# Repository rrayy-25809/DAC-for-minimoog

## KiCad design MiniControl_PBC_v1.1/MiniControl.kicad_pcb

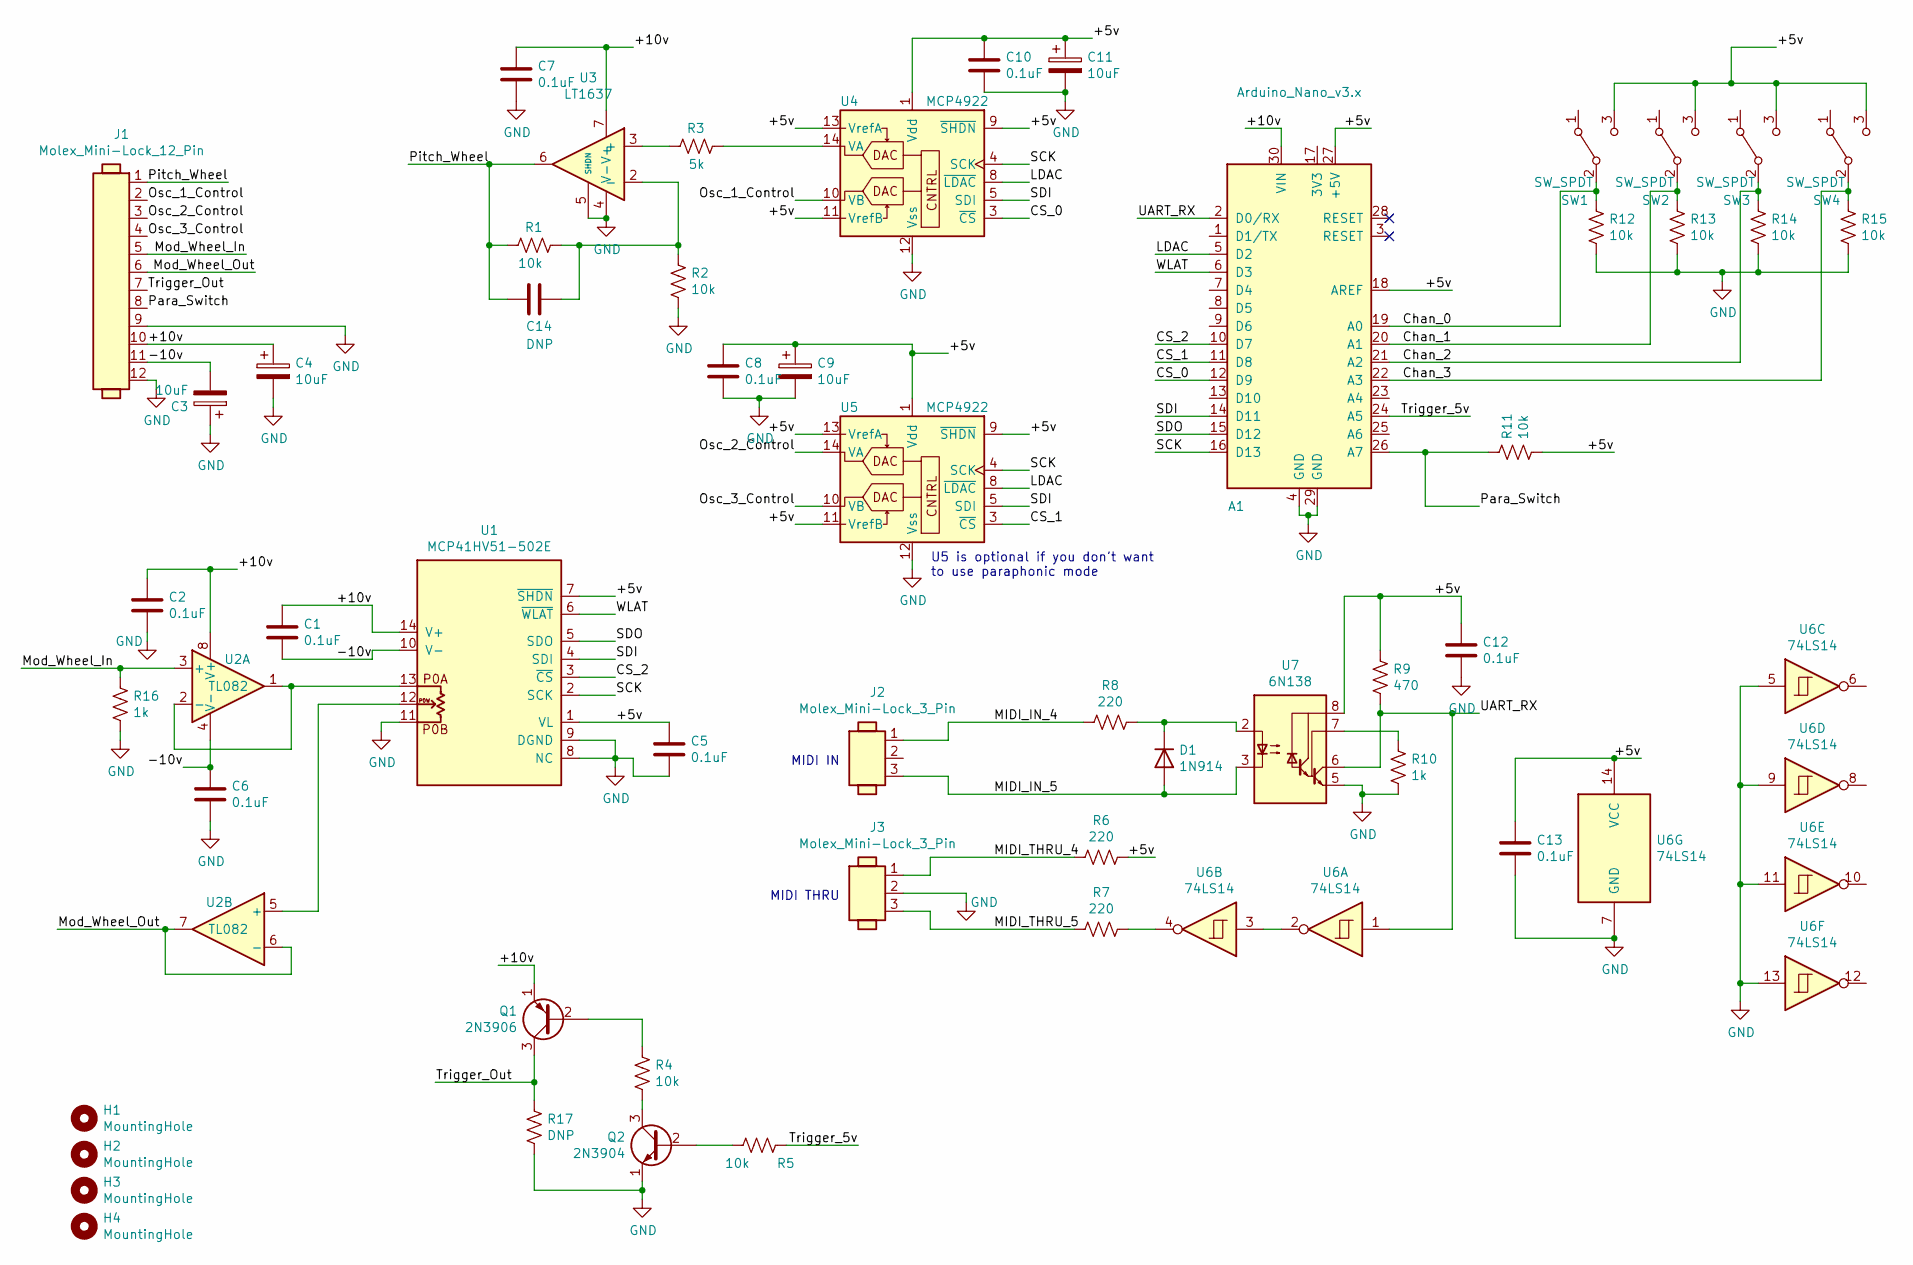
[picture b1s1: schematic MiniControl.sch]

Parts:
A1: Arduino_Nano_v3.x; Arduino_Nano
C1, C2, C5, C6, C7, C8, C10, C12, C13: 0.1uF; C_Disc_D5.1mm_W3.2mm_P5.00mm
C3, C4, C9, C11: 10uF; CP_Radial_Tantal_D6.0mm_P5.00mm
C14: DNP; C_Disc_D5.1mm_W3.2mm_P5.00mm
D1: 1N914; D_DO-35_SOD27_P7.62mm_Horizontal
H1, H2, H3, H4: MountingHole; MountingHole_3.2mm_M3
J1: Molex_Mini-Lock_12_Pin; Molex_Mini-Lock_0534261210_1x12_P2.50mm_Horizontal; Part # 0534261210
J2, J3: Molex_Mini-Lock_3_Pin; Molex_Mini-Lock_0534260310_1x03_P2.50mm_Horizontal; Part # 0534260310
Q1: 2N3906; TO-92_Inline
Q2: 2N3904; TO-92_Inline
R1, R2, R4, R5, R11, R12, R13, R14, R15: 10k; R_Axial_DIN0207_L6.3mm_D2.5mm_P10.16mm_Horizontal
R3: 5k; R_Axial_DIN0207_L6.3mm_D2.5mm_P10.16mm_Horizontal
R6, R7, R8: 220; R_Axial_DIN0207_L6.3mm_D2.5mm_P10.16mm_Horizontal
R9: 470; R_Axial_DIN0207_L6.3mm_D2.5mm_P10.16mm_Horizontal
R10, R16: 1k; R_Axial_DIN0207_L6.3mm_D2.5mm_P10.16mm_Horizontal
R17: DNP; R_Axial_DIN0207_L6.3mm_D2.5mm_P10.16mm_Horizontal
SW1, SW2, SW3, SW4: SW_SPDT; SW_Slide_SPDT_EG1218
U1: MCP41HV51-502E; TSSOP-14_4.4x5mm_P0.65mm
U2: TL082; DIP-8_W7.62mm_Socket
U3: LT1637; DIP-8_W7.62mm_Socket
U4, U5: MCP4922; DIP-14_W7.62mm_Socket
U6: 74LS14; DIP-14_W7.62mm_Socket
U7: 6N138; DIP-8_W7.62mm_Socket

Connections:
/+5v: A1.18 (AREF), A1.27 (+5V), C5.1, C8.1, C9.1, C10.1, C11.1, C12.1, C13.1, R6.2, R9.1, R11.2, SW1.3 (C), SW2.3 (C), SW3.3 (C), SW4.3 (C), U1.1 (VL), U1.7 (~SHDN), U4.1 (Vdd), U4.9 (~SHDN), U4.11 (VrefB), U4.13 (VrefA), U5.1 (Vdd), U5.9 (~SHDN), U5.11 (VrefB), U5.13 (VrefA), U6.14 (VCC), U7.8 (VCC)
/+10v: A1.30 (VIN), C1.1, C2.1, C4.1, C7.1, J1.10, Q1.1 (E), U1.14 (V+), U2.8 (V+), U3.7 (V+)
/-10v: C1.2, C3.2, C6.1, J1.11, U1.10 (V-), U2.4 (V-)
/CS_0: A1.12 (D9), U4.3 (~CS)
/CS_1: A1.11 (D8), U5.3 (~CS)
/CS_2: A1.10 (D7), U1.3 (~CS)
/CS_3: A1.9 (D6)
/Chan_0: A1.19 (A0), R12.1, SW1.2 (B)
/Chan_1: A1.20 (A1), R13.1, SW2.2 (B)
/Chan_2: A1.21 (A2), R14.1, SW3.2 (B)
/Chan_3: A1.22 (A3), R15.1, SW4.2 (B)
/LDAC: A1.5 (D2), U4.8 (~LDAC), U5.8 (~LDAC)
/MIDI_IN_4: J2.1, R8.1
/MIDI_IN_5: D1.2 (A), J2.3, U7.3 (C2)
/MIDI_THRU_4: J3.1, R6.1
/MIDI_THRU_5: J3.3, R7.1
/Mod_Wheel_In: J1.5, R16.1, U2.3 (+)
/Mod_Wheel_Out: J1.6, U2.6 (-), U2.7
/Osc_1_Control: J1.2, U4.10 (VB)
/Osc_2_Control: J1.3, U5.14 (VA)
/Osc_3_Control: J1.4, U5.10 (VB)
/Para_Switch: A1.26 (A7), J1.8, R11.1
/Pitch_Wheel: C14.2, J1.1, R1.1, U3.6
/SCK: A1.16 (D13), U1.2 (SCK), U4.4 (SCK), U5.4 (SCK)
/SDI: A1.14 (D11), U1.4 (SDI), U4.5 (SDI), U5.5 (SDI)
/SDO: A1.15 (D12), U1.5 (SDO)
/Trigger_5v: A1.24 (A5), R5.2
/Trigger_Out: J1.7, Q1.3 (C), R17.1
/UART_RX: A1.2 (D0/RX), R9.2, U6.1, U7.6 (VO2)
/WLAT: A1.6 (D3), U1.6 (~WLAT)
GND: A1.4 (GND), A1.29 (GND), C2.2, C3.1, C4.2, C5.2, C6.2, C7.2, C8.2, C9.2, C10.2, C11.2, C12.2, C13.2, J1.9, J1.12, J3.2, Q2.1 (E), R2.2, R10.2, R12.2, R13.2, R14.2, R15.2, R16.2, R17.2, U1.8 (NC), U1.9 (DGND), U1.11, U3.4 (V-), U3.5 (NC), U4.12 (Vss), U5.12 (Vss), U6.5, U6.7 (GND), U6.9, U6.11, U6.13, U7.5 (GND)
unnamed: C14.1, R1.2, R2.1, U3.2 (-)
unnamed: D1.1 (K), R8.2, U7.2 (C1)
unnamed: Q1.2 (B), R4.1
unnamed: Q2.2 (B), R5.1
unnamed: Q2.3 (C), R4.2
unnamed: R3.1, U3.3 (+)
unnamed: R3.2, U4.14 (VA)
unnamed: R7.2, U6.4
unnamed: R10.1, U7.7 (VO1)
unnamed: U1.12, U2.5 (+)
unnamed: U1.13, U2.1, U2.2 (-)
unnamed: U6.2, U6.3

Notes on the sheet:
MIDI IN
MIDI THRU
U5 is optional if you don't want to use paraphonic mode

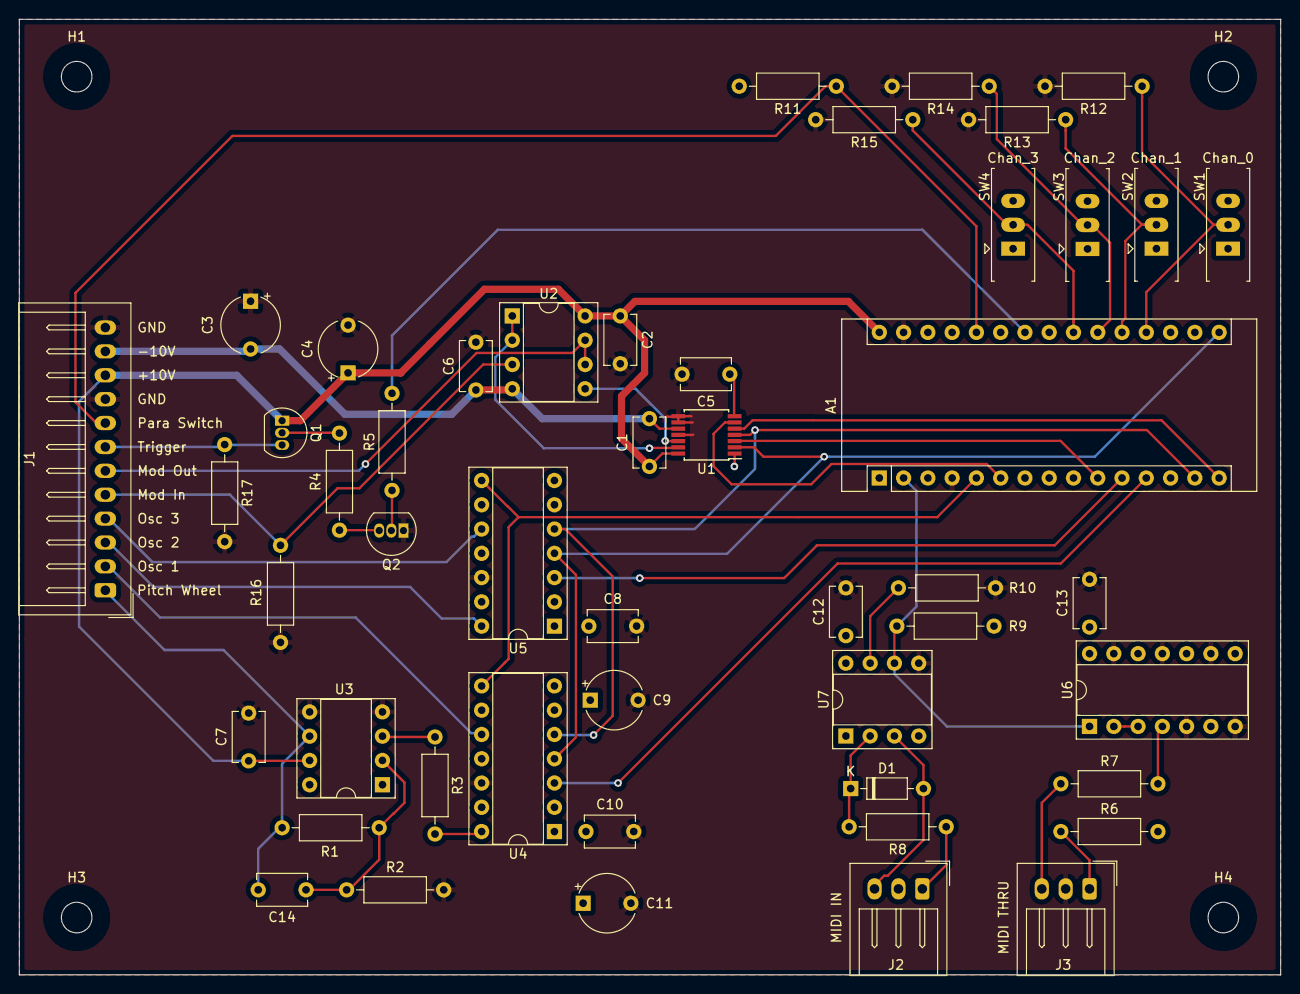
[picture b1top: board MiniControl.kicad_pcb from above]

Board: 2 copper layers, 132.0 x 100.0 mm, 53 parts (0 on the bottom side), 42 nets.

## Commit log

2025-04-23 Changes to be committed: platformio 사용 new file: .gitignore new file: .vscode/extensions.json new file: platformio.ini renamed: DAC.ino -> src/DAC.ino
2025-05-11 Changes to be committed: platformio 못 써먹겠음;; new file: .vscode/arduino.json deleted: .vscode/extensions.json new file: .vscode/settings.json renamed: src/DAC.ino -> DAC.ino deleted: platformio.ini
2025-06-24 Changes to be committed: 최적의 설정 찾아내는 중 modified: .vscode/arduino.json modified: .vscode/settings.json modified: DAC.ino
2025-07-26 Changes to be committed: noteList 해더 파일 설치, 아두이노 라이브러리 설정 실패 modified: .gitignore modified: .vscode/arduino.json new file: .vscode/c_cpp_properties.json modified: .vscode/settings.json new file: note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
2025-07-26 Changes to be committed: 미디 라이브러리 VScode에 적용 성공 modified: .vscode/c_cpp_properties.json
